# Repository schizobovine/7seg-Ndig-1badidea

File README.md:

7seg-Ndig-1badidea
==================

7-ish segment LED displays of varying amounts of digits

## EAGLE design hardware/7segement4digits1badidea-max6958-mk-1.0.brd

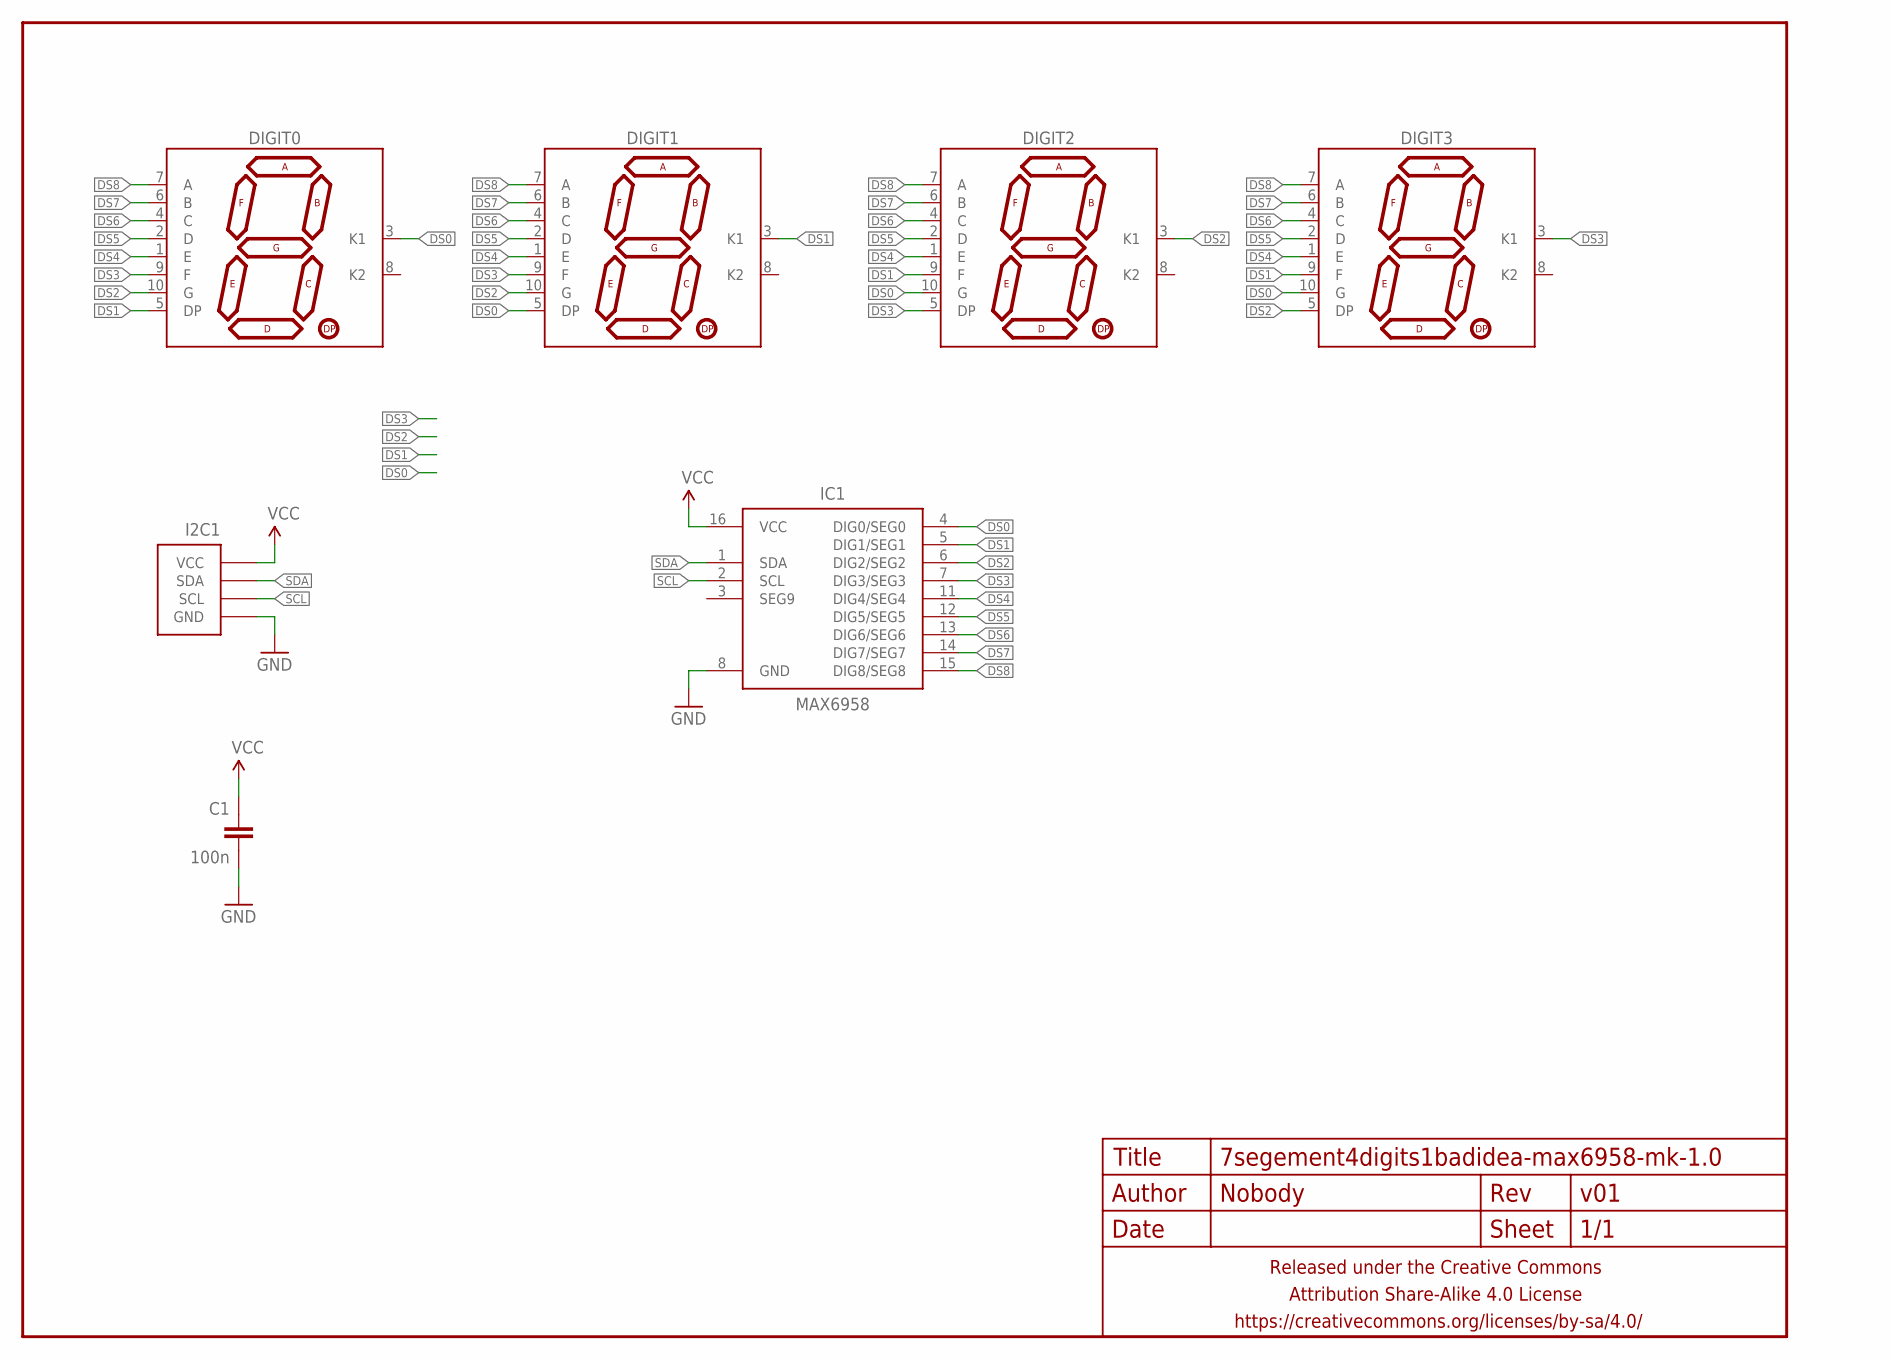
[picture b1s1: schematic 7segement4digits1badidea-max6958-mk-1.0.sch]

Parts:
C1: 100n; C025-024X044
DIGIT0, DIGIT1, DIGIT2, DIGIT3: 7SEG_1DIGPTH-25.4MM; 7SEG_1DIG_25.4MM
FRAME1: FRAME-LETTERNO_PACKAGE; DUMMY
I2C1: M04-I2CPTH-0.1IN-CENTERED; 1X04-PTH-VERT-I2C-CENTERED
IC1: MAX6958; DIL16

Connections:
DS0: DIGIT0.3 (K1), DIGIT1.5 (DP), DIGIT2.10 (G), DIGIT3.10 (G), IC1.4 (DIG0/SEG0)
DS1: DIGIT0.5 (DP), DIGIT1.3 (K1), DIGIT2.9 (F), DIGIT3.9 (F), IC1.5 (DIG1/SEG1)
DS2: DIGIT0.10 (G), DIGIT1.10 (G), DIGIT2.3 (K1), DIGIT3.5 (DP), IC1.6 (DIG2/SEG2)
DS3: DIGIT0.9 (F), DIGIT1.9 (F), DIGIT2.5 (DP), DIGIT3.3 (K1), IC1.7 (DIG3/SEG3)
DS4: DIGIT0.1 (E), DIGIT1.1 (E), DIGIT2.1 (E), DIGIT3.1 (E), IC1.11 (DIG4/SEG4)
DS5: DIGIT0.2 (D), DIGIT1.2 (D), DIGIT2.2 (D), DIGIT3.2 (D), IC1.12 (DIG5/SEG5)
DS6: DIGIT0.4 (C), DIGIT1.4 (C), DIGIT2.4 (C), DIGIT3.4 (C), IC1.13 (DIG6/SEG6)
DS7: DIGIT0.6 (B), DIGIT1.6 (B), DIGIT2.6 (B), DIGIT3.6 (B), IC1.14 (DIG7/SEG7)
DS8: DIGIT0.7 (A), DIGIT1.7 (A), DIGIT2.7 (A), DIGIT3.7 (A), IC1.15 (DIG8/SEG8)
GND: C1.2, I2C1.GND, IC1.8 (GND)
SCL: I2C1.SCL, IC1.2 (SCL)
SDA: I2C1.SDA, IC1.1 (SDA)
VCC: C1.1, I2C1.VCC, IC1.16 (VCC)

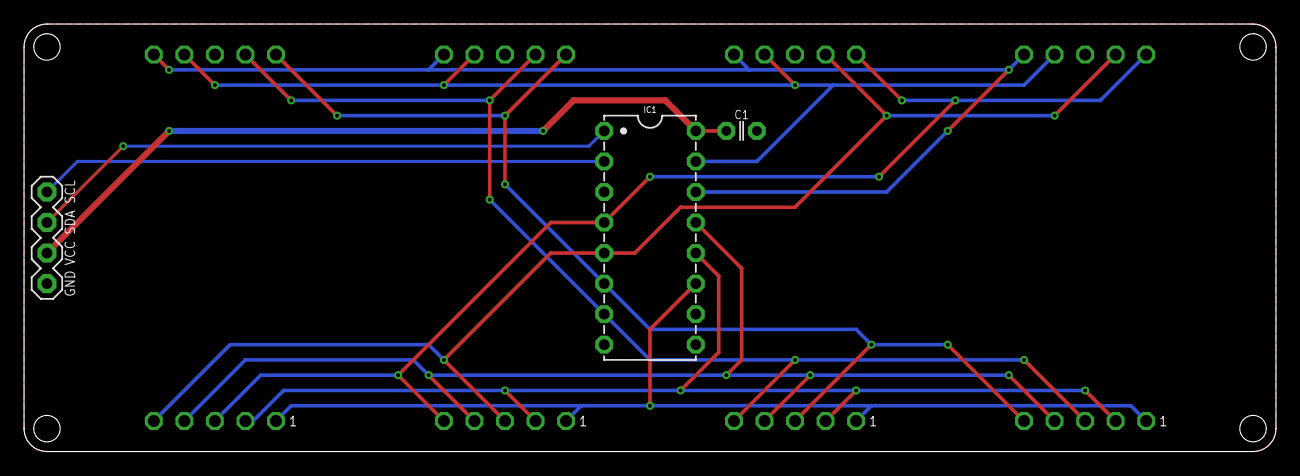
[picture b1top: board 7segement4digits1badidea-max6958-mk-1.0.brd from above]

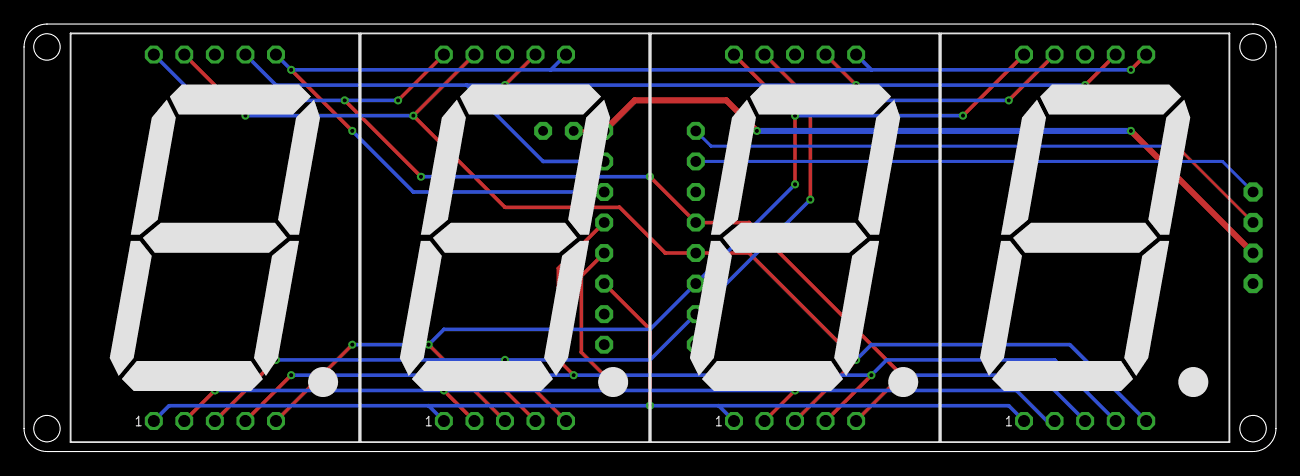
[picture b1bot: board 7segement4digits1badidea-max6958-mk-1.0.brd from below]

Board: 2 copper layers, 104.1 x 35.6 mm, 8 parts (4 on the bottom side), 13 nets.

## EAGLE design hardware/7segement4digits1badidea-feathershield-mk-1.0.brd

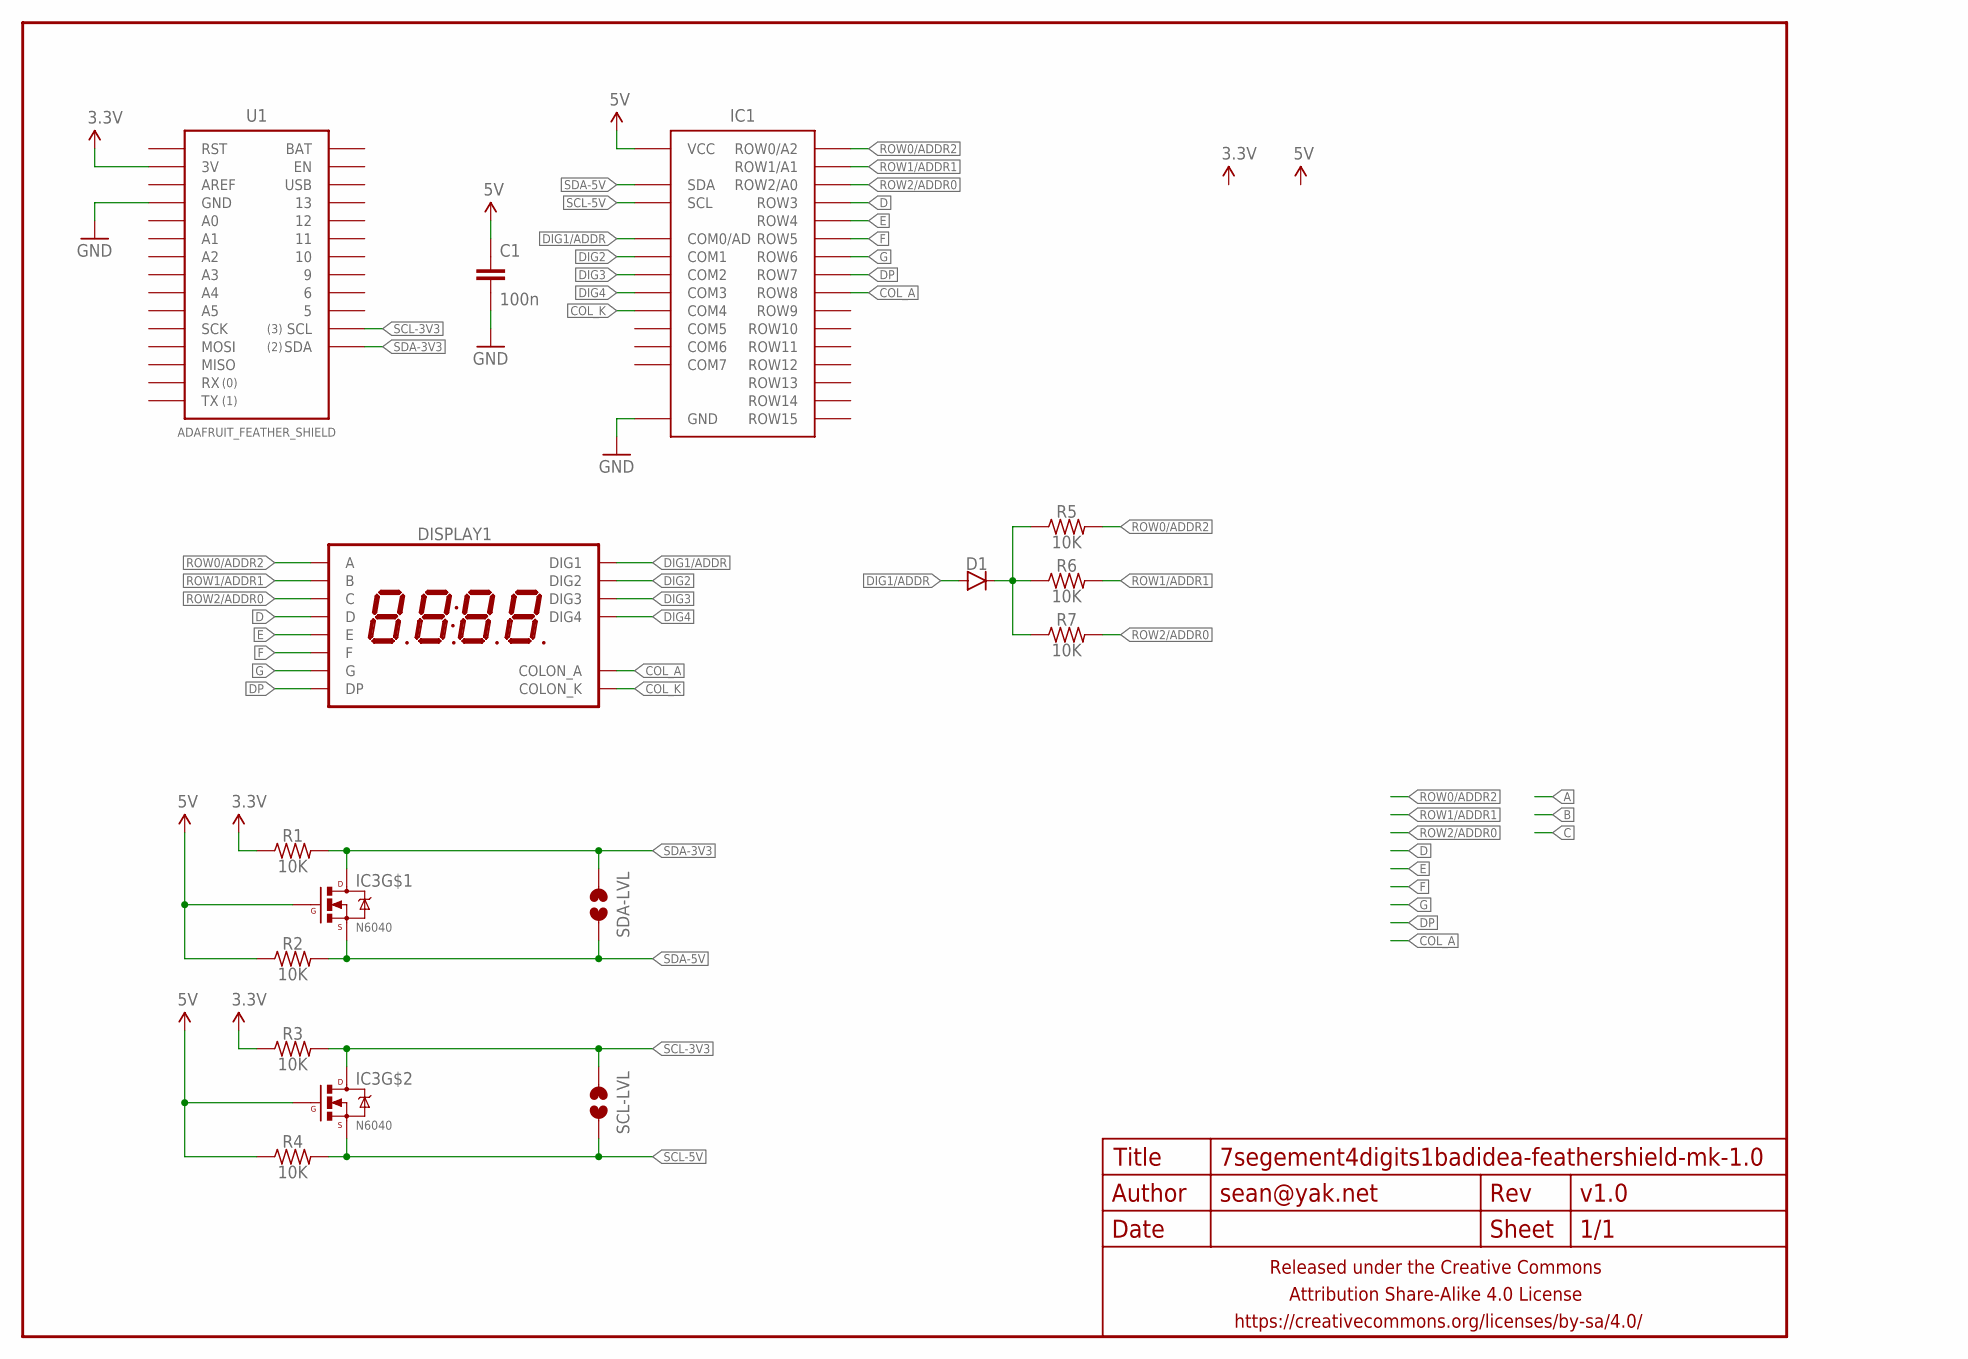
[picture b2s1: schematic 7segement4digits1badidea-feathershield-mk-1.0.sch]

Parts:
C1: 100n; C0603
D1: DIODESOT23; SOT23
DISPLAY1: 7SEG_4DIGIT_COLON14.2MM-CC; 7SEG_4DIG_0.56IN_14MM_ADAFRUIT
FRAME1: FRAME-LETTERNO_PACKAGE; DUMMY
IC1: HT16K33; SOIC28W
IC3: N6040; SO08
R1, R2, R3, R4, R5, R6, R7: 10K; R0603
SCL-LVL: JUMPER-PAD-2-NOYES_SILK; PAD-JUMPER-2-NO_YES_SILK
SDA-LVL: JUMPER-PAD-2-NOYES_SILK; PAD-JUMPER-2-NO_YES_SILK
U1: ADAFRUIT_FEATHER_SHIELD; ADAFRUIT_FEATHER

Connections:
3.3V: R1.1, R3.1, U1.3V
5V: C1.1, IC1.28 (VCC), IC3.2 (G), IC3.4 (G), R2.1, R4.1
COL_A: DISPLAY1.P$8 (COLON_A), IC1.17 (ROW8)
COL_K: DISPLAY1.P$7 (COLON_K), IC1.6 (COM4)
D: DISPLAY1.P$2 (D), IC1.22 (ROW3)
DIG1/ADDR: D1.1 (A), DISPLAY1.P$14 (DIG1), IC1.2 (COM0/AD)
DIG2: DISPLAY1.P$11 (DIG2), IC1.3 (COM1)
DIG3: DISPLAY1.P$10 (DIG3), IC1.4 (COM2)
DIG4: DISPLAY1.P$6 (DIG4), IC1.5 (COM3)
DP: DISPLAY1.P$3 (DP), IC1.18 (ROW7)
E: DISPLAY1.P$1 (E), IC1.21 (ROW4)
F: DISPLAY1.P$12 (F), IC1.20 (ROW5)
G: DISPLAY1.P$5 (G), IC1.19 (ROW6)
GND: C1.2, IC1.1 (GND), U1.GND@0 (GND), U1.GND@1 (GND)
unnamed: D1.3 (C), R5.1, R6.1, R7.1
ROW0/ADDR2: DISPLAY1.P$13 (A), IC1.25 (ROW0/A2), R5.2
ROW1/ADDR1: DISPLAY1.P$9 (B), IC1.24 (ROW1/A1), R6.2
ROW2/ADDR0: DISPLAY1.P$4 (C), IC1.23 (ROW2/A0), R7.2
SCL-3V3: IC3.5 (D), IC3.6 (D), R3.2, SCL-LVL.1, U1.SCL
SCL-5V: IC1.26 (SCL), IC3.3 (S), R4.2, SCL-LVL.2
SDA-3V3: IC3.7 (D), IC3.8 (D), R1.2, SDA-LVL.1, U1.SDA
SDA-5V: IC1.27 (SDA), IC3.1 (S), R2.2, SDA-LVL.2

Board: 2 copper layers, 16 parts (2 on the bottom side), 22 nets, no tracks yet.

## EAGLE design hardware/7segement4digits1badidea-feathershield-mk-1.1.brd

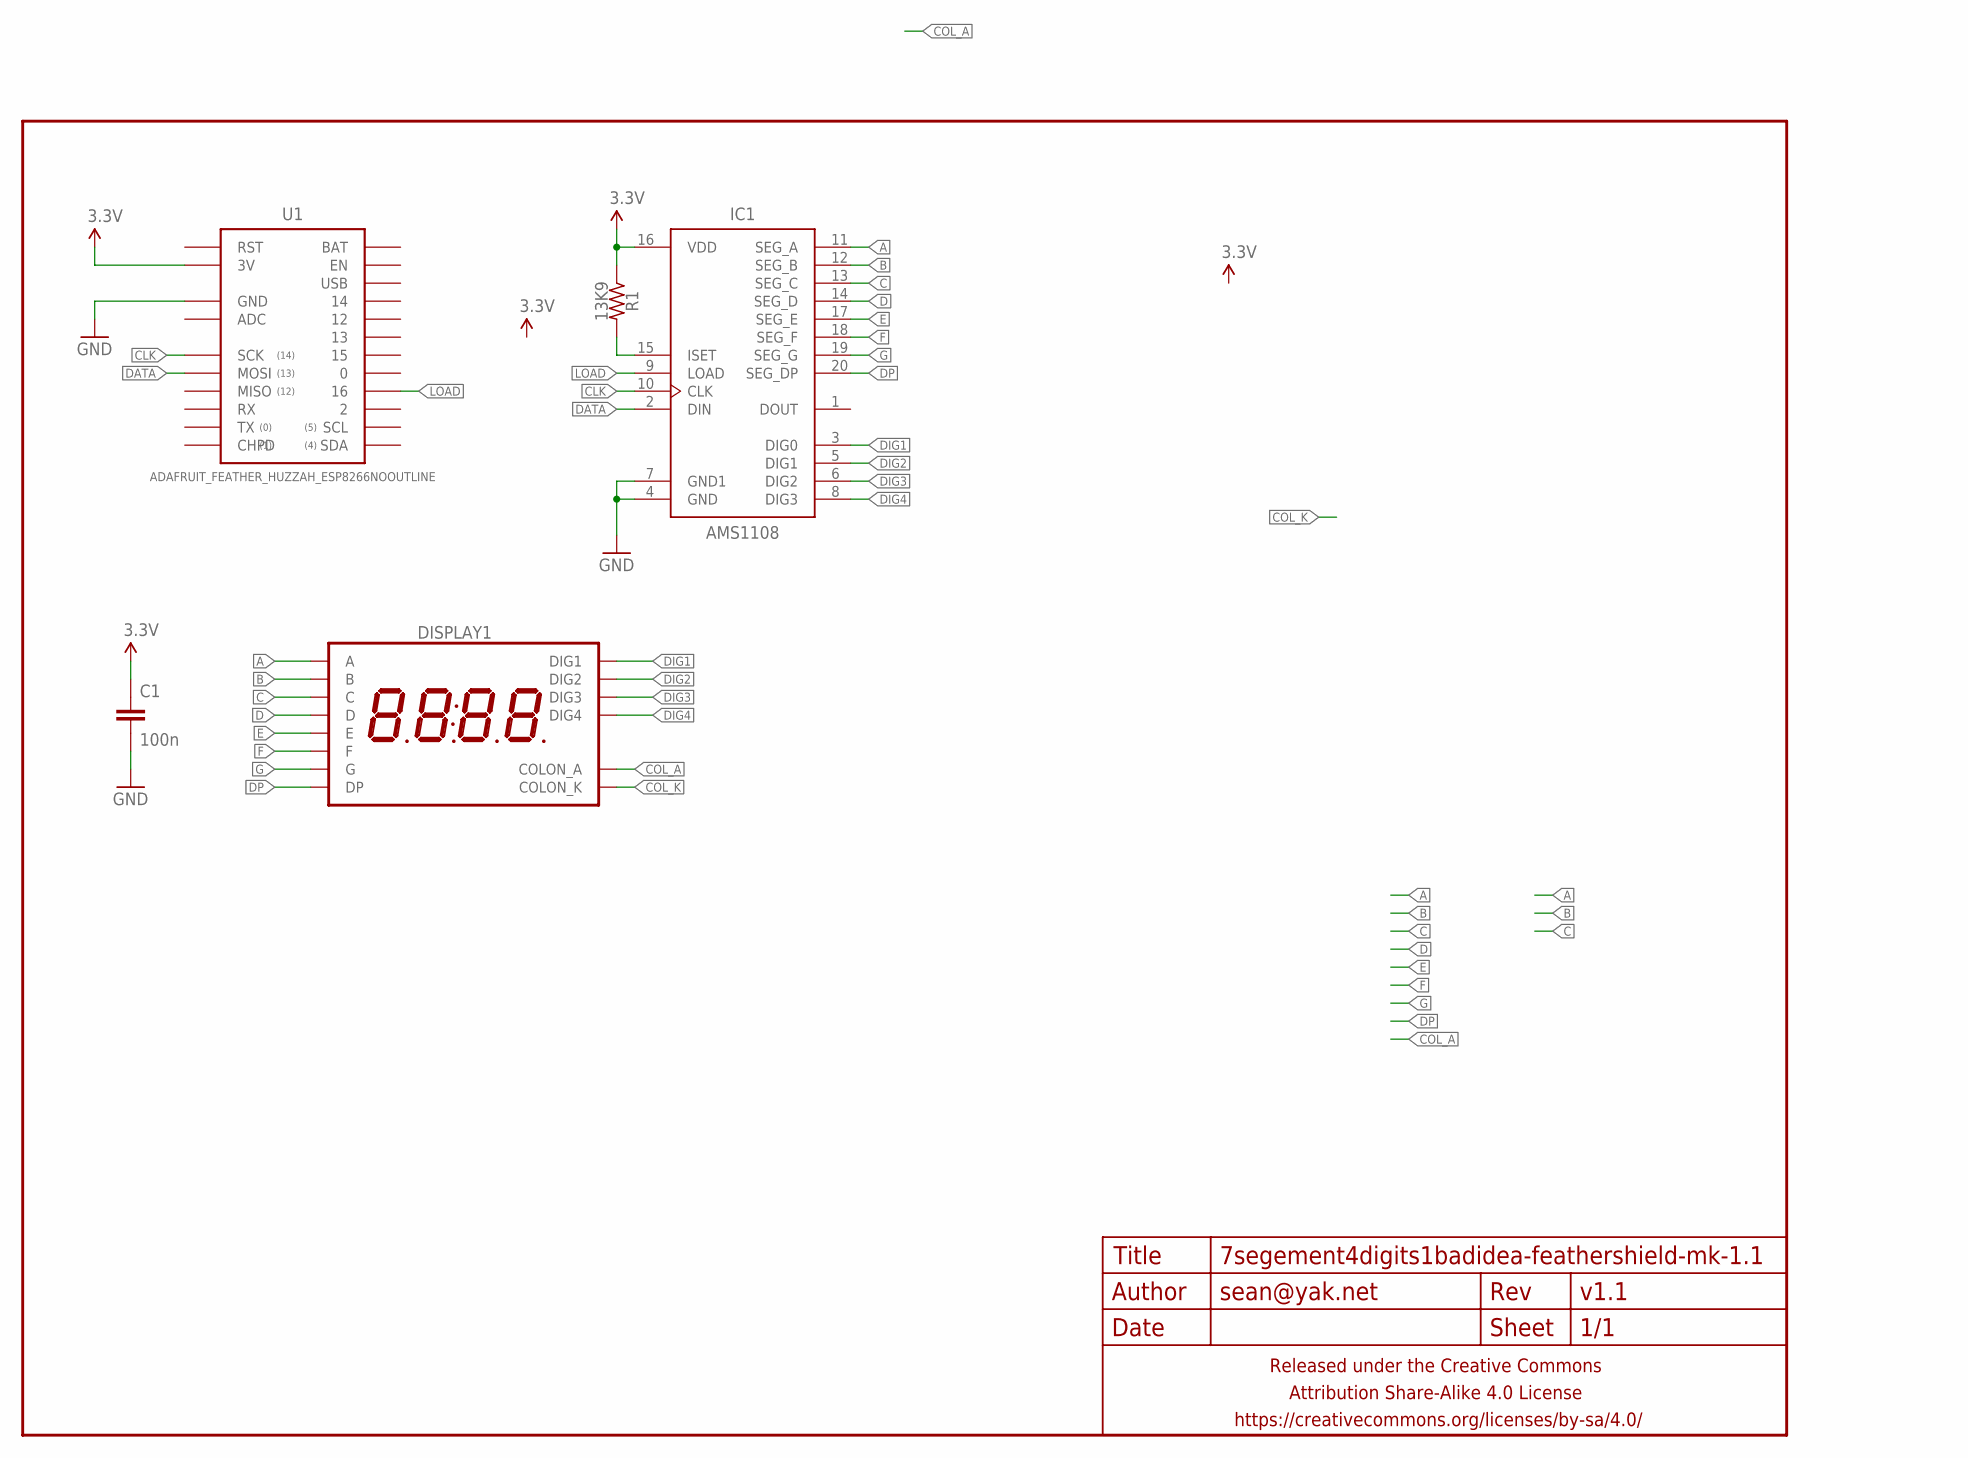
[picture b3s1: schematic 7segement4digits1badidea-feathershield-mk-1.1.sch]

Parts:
C1: 100n; C0603
DISPLAY1: 7SEG_4DIGIT_COLON14.2MM-CC; 7SEG_4DIG_0.56IN_14MM_ADAFRUIT
FRAME1: FRAME-LETTERNO_PACKAGE; DUMMY
IC1: AMS1108; SO20W-NOSUCK
R1: 13K9; R0603
U1: ADAFRUIT_FEATHER_HUZZAH_ESP8266NOOUTLINE; ADAFRUIT_FEATHER_HUZZAH_NOOUTLINE

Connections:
3.3V: C1.1, IC1.16 (VDD), R1.1, U1.3V
A: DISPLAY1.P$13 (A), IC1.11 (SEG_A)
B: DISPLAY1.P$9 (B), IC1.12 (SEG_B)
C: DISPLAY1.P$4 (C), IC1.13 (SEG_C)
CLK: IC1.10 (CLK), U1.SCK
COL_A: DISPLAY1.P$8 (COLON_A)
COL_K: DISPLAY1.P$7 (COLON_K)
D: DISPLAY1.P$2 (D), IC1.14 (SEG_D)
DATA: IC1.2 (DIN), U1.MOSI
DIG1: DISPLAY1.P$14 (DIG1), IC1.3 (DIG0)
DIG2: DISPLAY1.P$11 (DIG2), IC1.5 (DIG1)
DIG3: DISPLAY1.P$10 (DIG3), IC1.6 (DIG2)
DIG4: DISPLAY1.P$6 (DIG4), IC1.8 (DIG3)
DP: DISPLAY1.P$3 (DP), IC1.20 (SEG_DP)
E: DISPLAY1.P$1 (E), IC1.17 (SEG_E)
F: DISPLAY1.P$12 (F), IC1.18 (SEG_F)
G: DISPLAY1.P$5 (G), IC1.19 (SEG_G)
GND: C1.2, IC1.4 (GND), IC1.7 (GND1), U1.GND@0 (GND)
LOAD: IC1.9 (LOAD), U1.16
unnamed: IC1.15 (ISET), R1.2

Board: 2 copper layers, 6 parts (2 on the bottom side), 18 nets, no tracks yet.

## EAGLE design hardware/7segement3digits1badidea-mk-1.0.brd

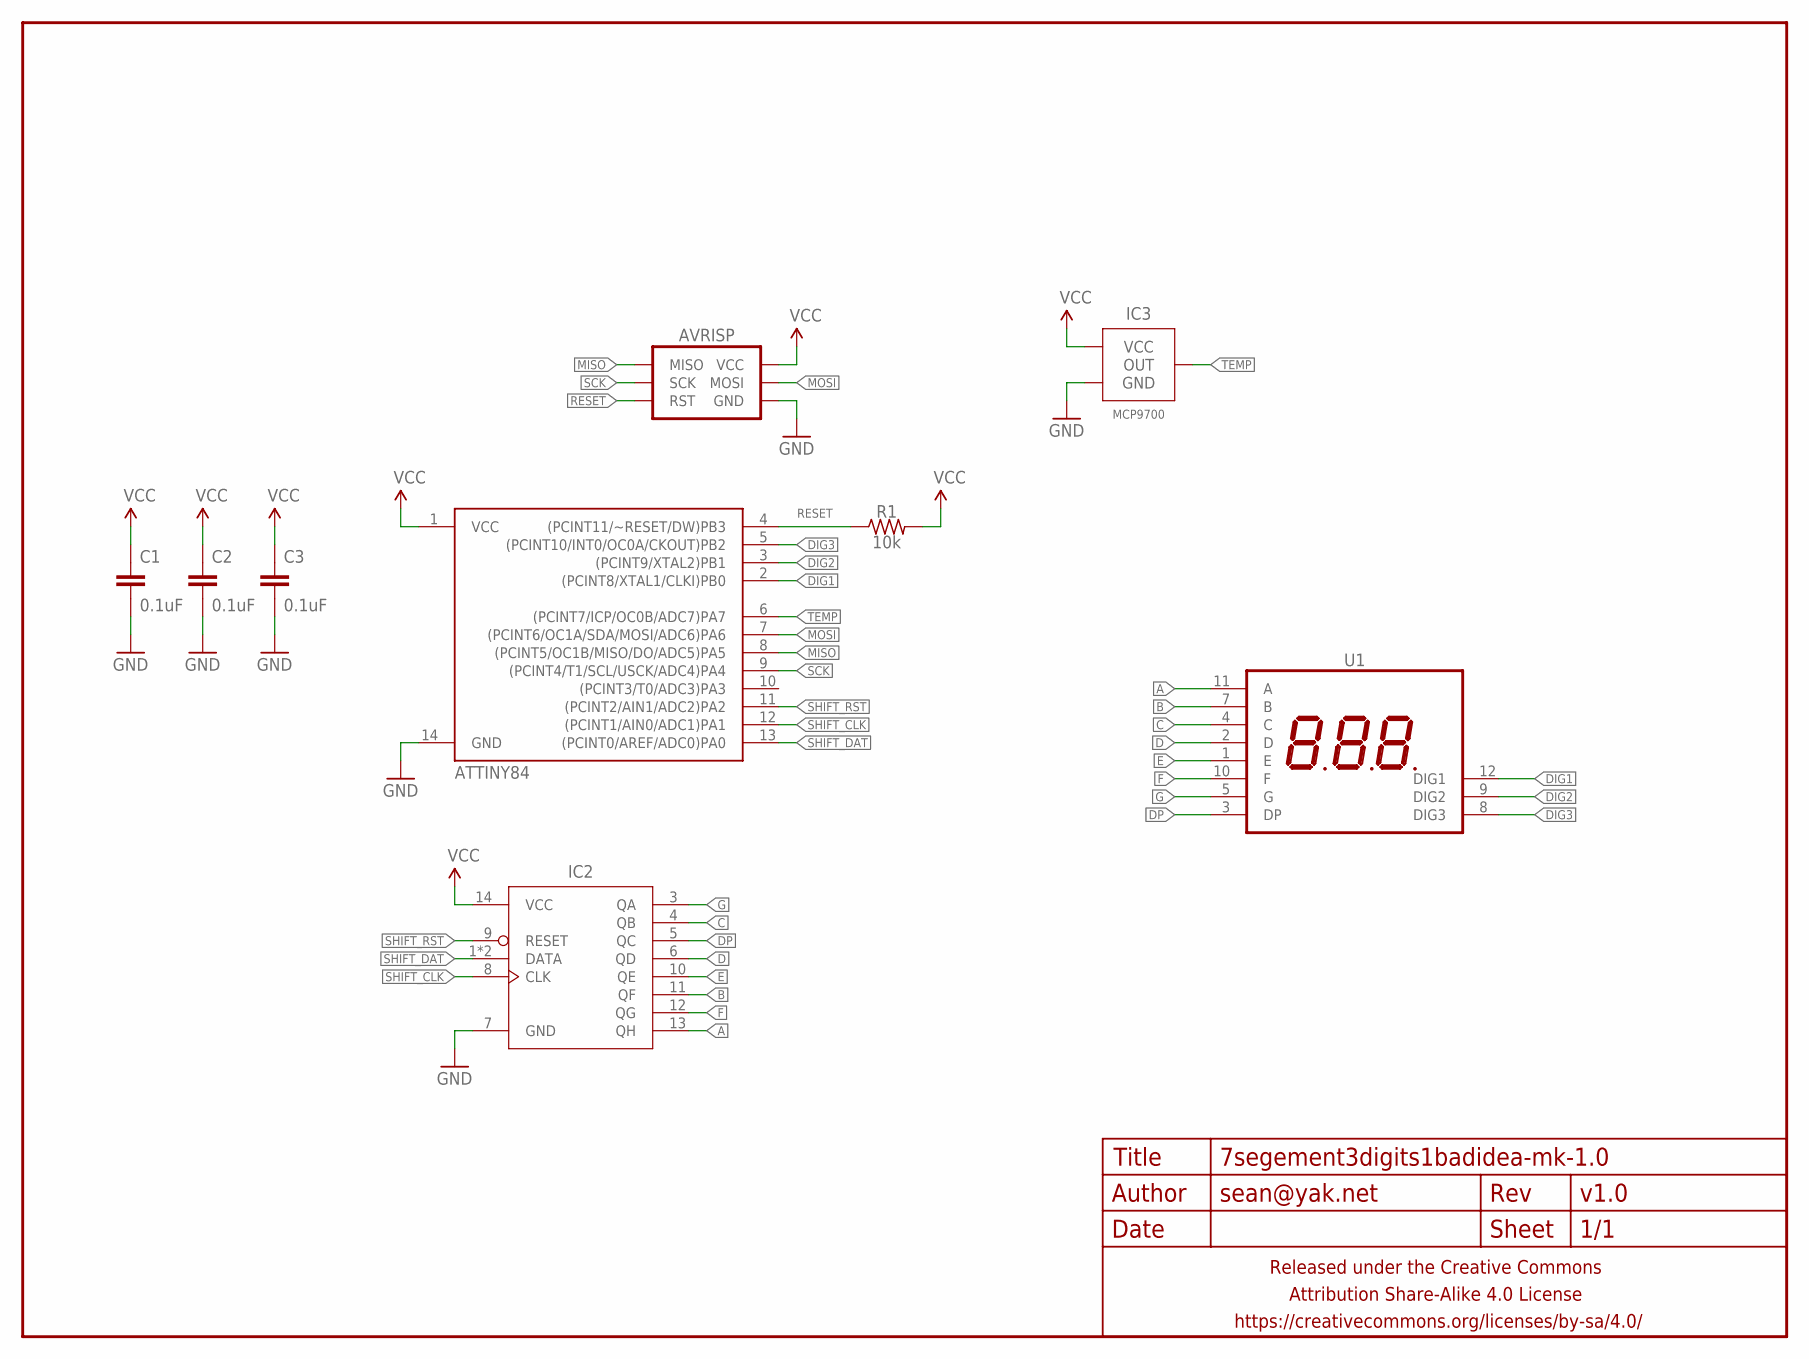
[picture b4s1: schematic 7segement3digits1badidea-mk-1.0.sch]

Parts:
AVRISP: AVR_SPI_PRG_6PTH_INLINE_I2C; AVR_ISP_INLINE_PTH_I2C
C1, C2, C3: 0.1uF; C0603
FRAME1: FRAME-LETTERNO_PACKAGE; DUMMY
IC1: ATTINY84; SO14
IC2: 74HC164; SO14
IC3: MCP9700; SOT23
R1: 10k; R0603
U1: 7SEG_3DIGIT; 7SEG_3DIG_0.56IN

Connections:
A: IC2.13 (QH), U1.11 (A)
B: IC2.11 (QF), U1.7 (B)
C: IC2.4 (QB), U1.4 (C)
D: IC2.6 (QD), U1.2 (D)
DIG1: IC1.2 ((PCINT8/XTAL1/CLKI)PB0), U1.12 (DIG1)
DIG2: IC1.3 ((PCINT9/XTAL2)PB1), U1.9 (DIG2)
DIG3: IC1.5 ((PCINT10/INT0/OC0A/CKOUT)PB2), U1.8 (DIG3)
DP: IC2.5 (QC), U1.3 (DP)
E: IC2.10 (QE), U1.1 (E)
F: IC2.12 (QG), U1.10 (F)
G: IC2.3 (QA), U1.5 (G)
GND: AVRISP.GND, C1.2, C2.2, C3.2, IC1.14 (GND), IC2.7 (GND), IC3.3 (GND)
MISO: AVRISP.MISO, IC1.8 ((PCINT5/OC1B/MISO/DO/ADC5)PA5)
MOSI: AVRISP.MOSI, IC1.7 ((PCINT6/OC1A/SDA/MOSI/ADC6)PA6)
RESET: AVRISP.RESET (RST), IC1.4 ((PCINT11/~RESET/DW)PB3), R1.1
SCK: AVRISP.SCK, IC1.9 ((PCINT4/T1/SCL/USCK/ADC4)PA4)
SHIFT_CLK: IC1.12 ((PCINT1/AIN0/ADC1)PA1), IC2.8 (CLK)
SHIFT_DAT: IC1.13 ((PCINT0/AREF/ADC0)PA0), IC2.1 (DATA), IC2.2 (DATA)
SHIFT_RST: IC1.11 ((PCINT2/AIN1/ADC2)PA2), IC2.9 (RESET)
TEMP: IC1.6 ((PCINT7/ICP/OC0B/ADC7)PA7), IC3.2 (OUT)
VCC: AVRISP.VCC, C1.1, C2.1, C3.1, IC1.1 (VCC), IC2.14 (VCC), IC3.1 (VCC), R1.2

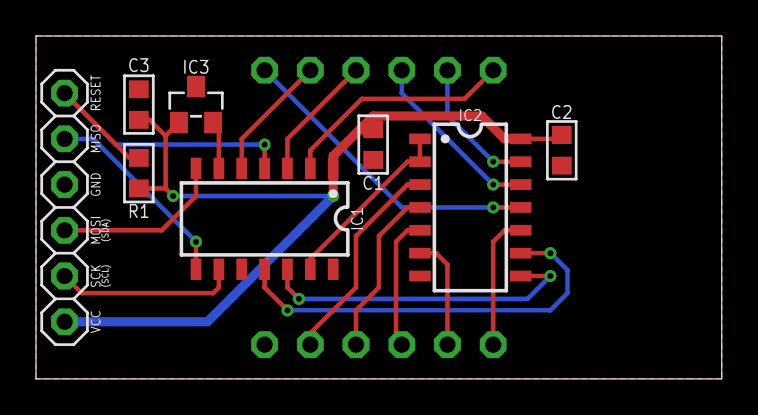
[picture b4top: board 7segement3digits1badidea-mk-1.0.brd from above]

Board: 2 copper layers, 38.1 x 19.1 mm, 10 parts (1 on the bottom side), 21 nets.

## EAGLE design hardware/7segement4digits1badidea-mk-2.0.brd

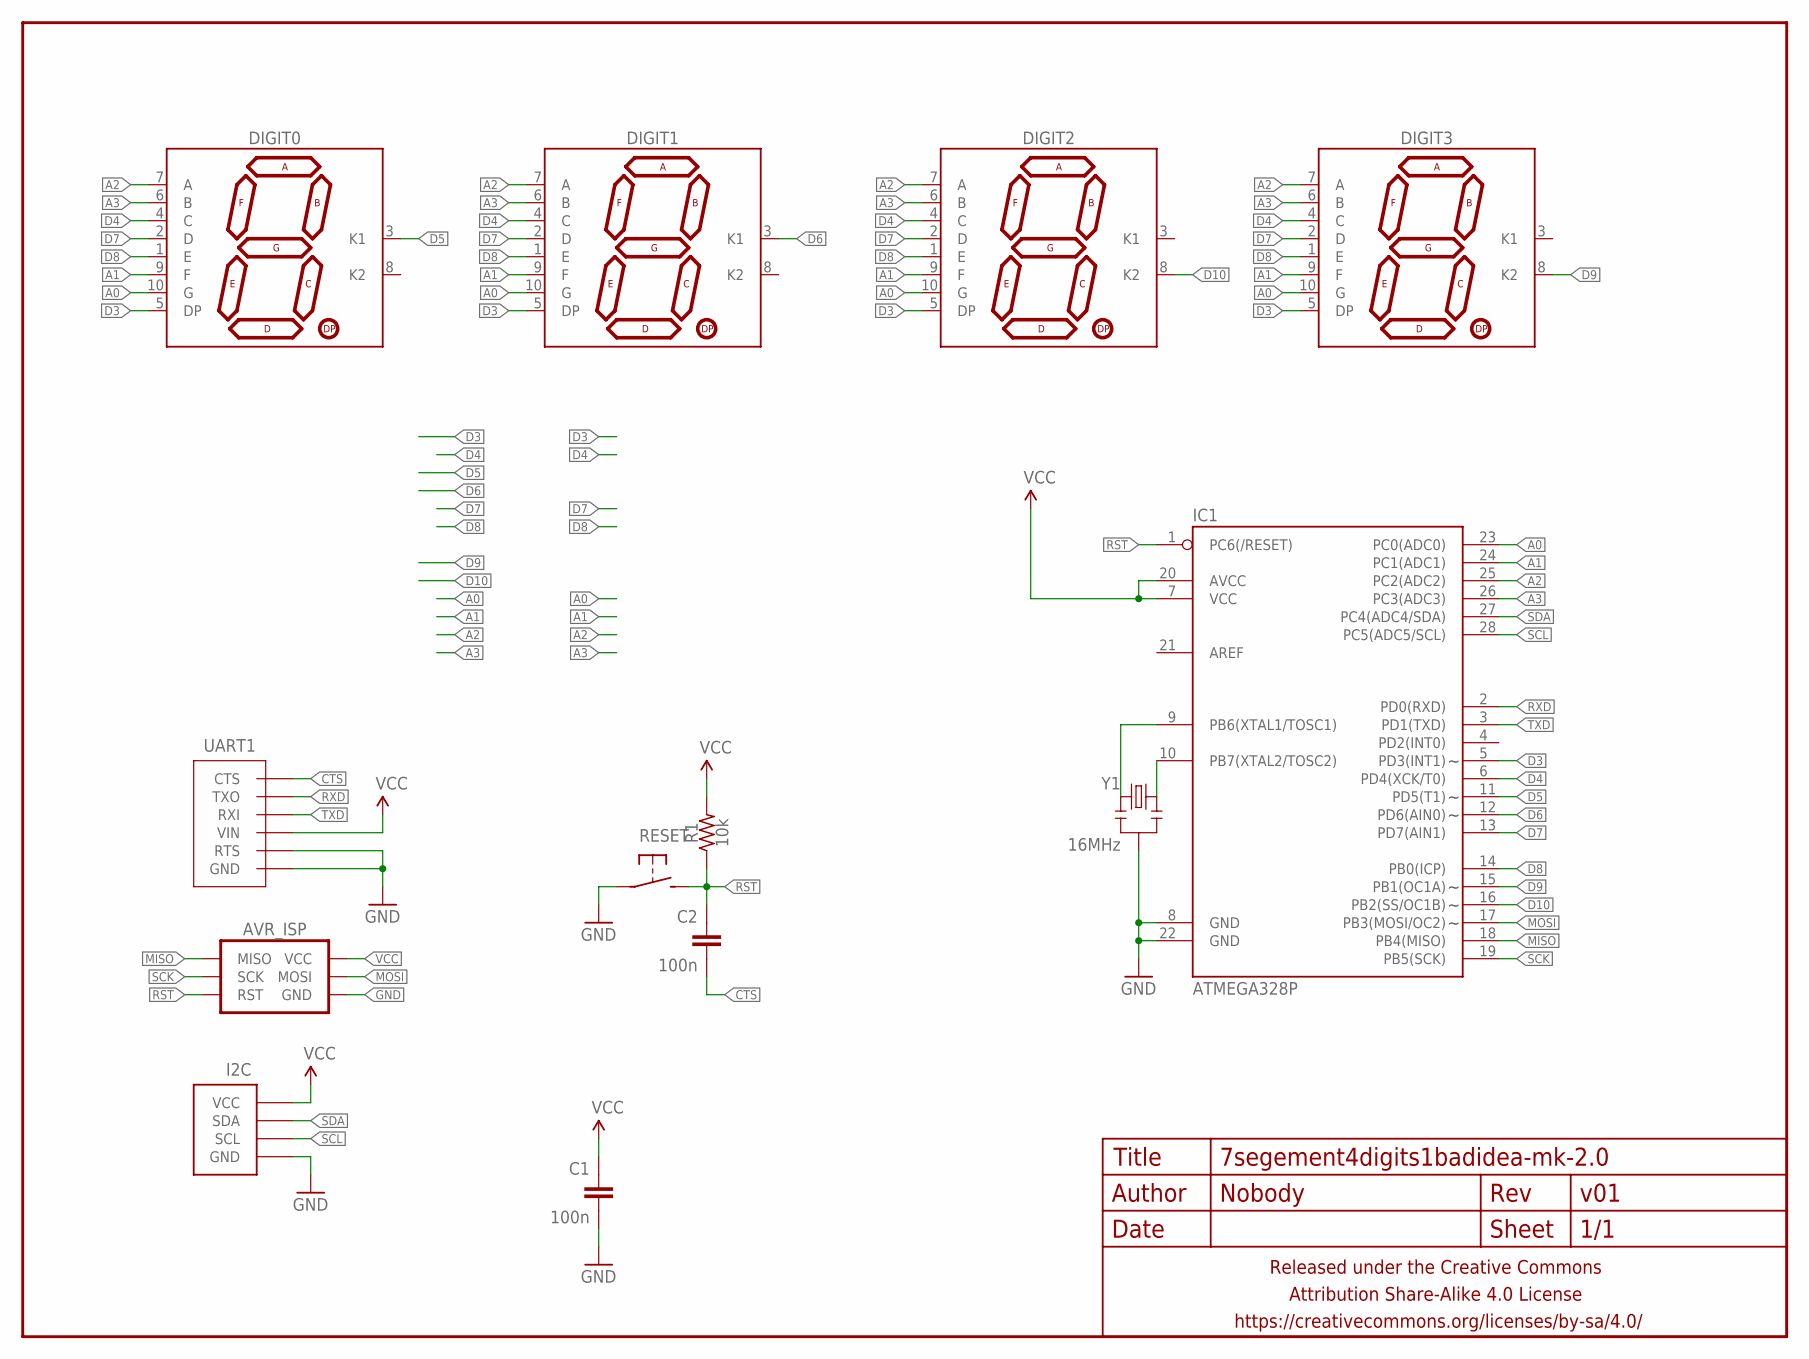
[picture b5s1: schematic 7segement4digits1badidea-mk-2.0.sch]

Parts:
AVR_ISP: AVR_SPI_PRG_6PTH; 2X3
C1, C2: 100n; C025-024X044
DIGIT0, DIGIT1, DIGIT2, DIGIT3: 7SEG_1DIGPTH-25.4MM; 7SEG_1DIG_25.4MM
FRAME1: FRAME-LETTERNO_PACKAGE; DUMMY
I2C: M04-I2CPTH-0.1IN-CENTERED-FLIPPED; 1X04-PTH-VERT-I2C-CENTERED-FLIPPED
IC1: ATMEGA328P; DIL28-3
R1: 10k; RESISTOR-AXIAL-PTH-7.62MM
RESET: SPST-NO-TACT3MM-PTH-SMALL-PADS; DTS-3-SMALL-PADS
UART1: M06-UARTPTH-0.1IN; 1X06_PTH_UART
Y1: 16MHz; RESONATOR-PTH

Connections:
A0: DIGIT0.10 (G), DIGIT1.10 (G), DIGIT2.10 (G), DIGIT3.10 (G), IC1.23 (PC0(ADC0))
A1: DIGIT0.9 (F), DIGIT1.9 (F), DIGIT2.9 (F), DIGIT3.9 (F), IC1.24 (PC1(ADC1))
A2: DIGIT0.7 (A), DIGIT1.7 (A), DIGIT2.7 (A), DIGIT3.7 (A), IC1.25 (PC2(ADC2))
A3: DIGIT0.6 (B), DIGIT1.6 (B), DIGIT2.6 (B), DIGIT3.6 (B), IC1.26 (PC3(ADC3))
CTS: C2.2, UART1.CTS
D3: DIGIT0.5 (DP), DIGIT1.5 (DP), DIGIT2.5 (DP), DIGIT3.5 (DP), IC1.5 (PD3(INT1))
D4: DIGIT0.4 (C), DIGIT1.4 (C), DIGIT2.4 (C), DIGIT3.4 (C), IC1.6 (PD4(XCK/T0))
D5: DIGIT0.3 (K1), IC1.11 (PD5(T1))
D6: DIGIT1.3 (K1), IC1.12 (PD6(AIN0))
D7: DIGIT0.2 (D), DIGIT1.2 (D), DIGIT2.2 (D), DIGIT3.2 (D), IC1.13 (PD7(AIN1))
D8: DIGIT0.1 (E), DIGIT1.1 (E), DIGIT2.1 (E), DIGIT3.1 (E), IC1.14 (PB0(ICP))
D9: DIGIT3.8 (K2), IC1.15 (PB1(OC1A))
D10: DIGIT2.8 (K2), IC1.16 (PB2(SS/OC1B))
GND: AVR_ISP.6 (GND), C1.2, I2C.GND, IC1.8 (GND), IC1.22 (GND), RESET.1, UART1.GND, UART1.RTS, Y1.2
MISO: AVR_ISP.1 (MISO), IC1.18 (PB4(MISO))
MOSI: AVR_ISP.4 (MOSI), IC1.17 (PB3(MOSI/OC2))
unnamed: IC1.10 (PB7(XTAL2/TOSC2)), Y1.1
unnamed: IC1.9 (PB6(XTAL1/TOSC1)), Y1.3
RST: AVR_ISP.5 (RST), C2.1, IC1.1 (PC6(/RESET)), R1.P$1 (1), RESET.2
RXD: IC1.2 (PD0(RXD)), UART1.TXO
SCK: AVR_ISP.3 (SCK), IC1.19 (PB5(SCK))
SCL: I2C.SCL, IC1.28 (PC5(ADC5/SCL))
SDA: I2C.SDA, IC1.27 (PC4(ADC4/SDA))
TXD: IC1.3 (PD1(TXD)), UART1.RXI
VCC: AVR_ISP.2 (VCC), C1.1, I2C.VCC, IC1.7 (VCC), IC1.20 (AVCC), R1.P$2 (2), UART1.VCC (VIN)

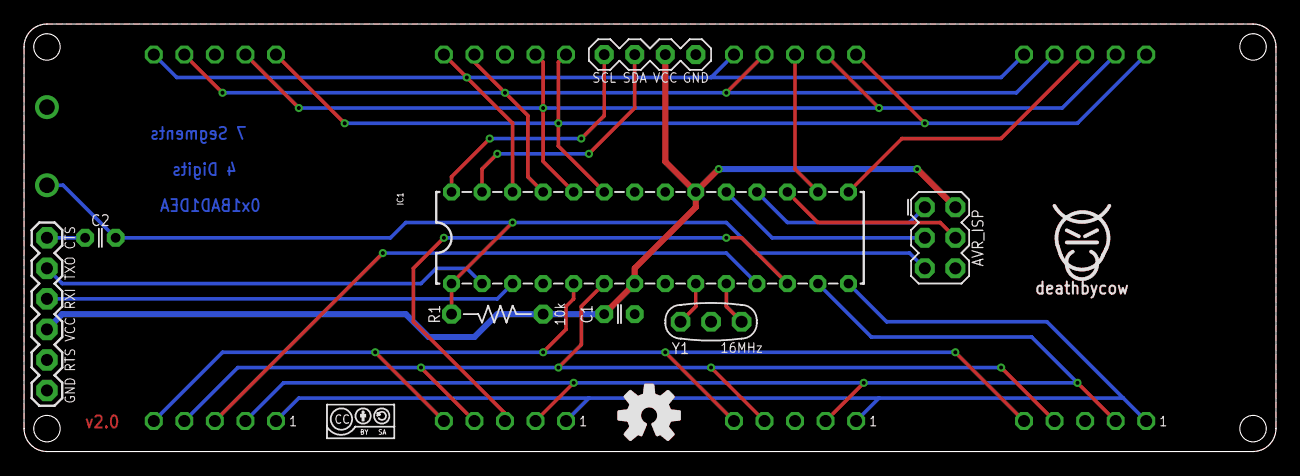
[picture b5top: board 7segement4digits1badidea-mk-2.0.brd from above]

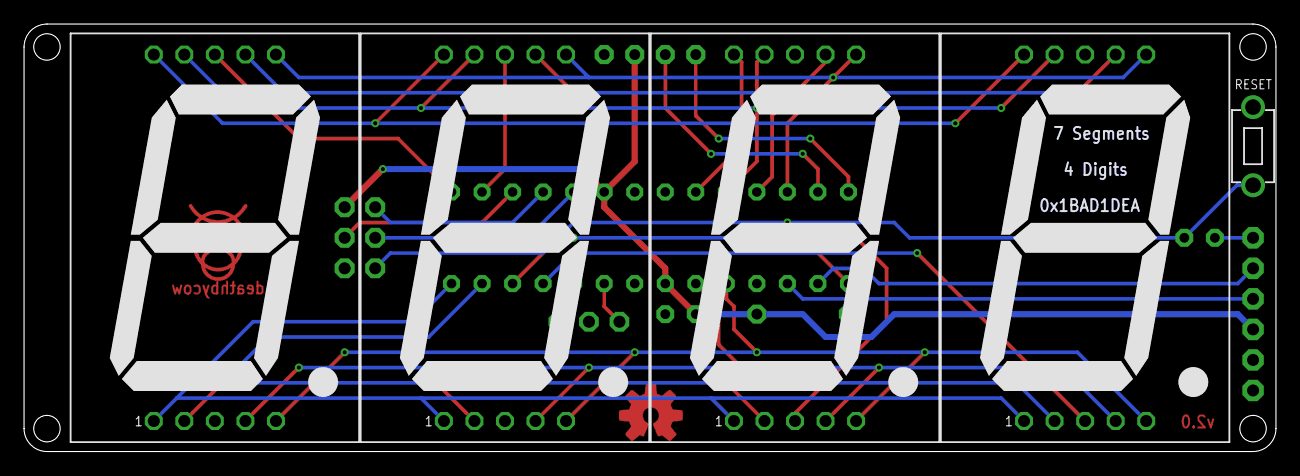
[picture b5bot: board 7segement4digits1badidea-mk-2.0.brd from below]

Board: 2 copper layers, 104.1 x 35.6 mm, 17 parts (5 on the bottom side), 25 nets.

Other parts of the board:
U$1: CC-BY-SA-4.0-NO-URL
U$2: COW_SMALL_METAL
U$3: OSHWLOGO_TOP_0.2_A

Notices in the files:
parts and their libraries:
SparkFun-Aesthetics: Licensing: Creative Commons ShareAlike 4.0 International - https://creativecommons.org/licenses/by-sa/4.0
A_butts: Released under the Creative Commons Attribution Share-Alike 4.0 License
A_butts: https://creativecommons.org/licenses/by-sa/4.0
